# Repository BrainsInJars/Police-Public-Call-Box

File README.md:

Police-Public-Call-Box
======================

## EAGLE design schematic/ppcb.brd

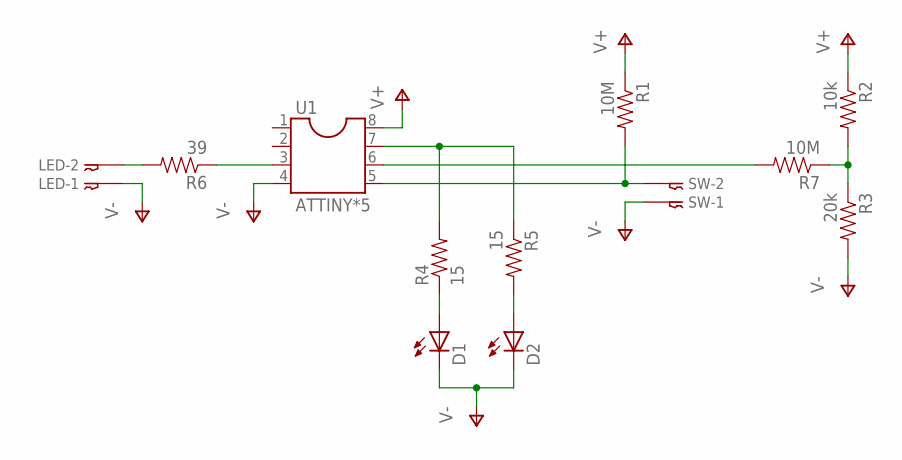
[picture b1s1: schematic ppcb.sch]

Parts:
D1, D2: LED5MM
LED: 02-JST; B2B-XH
R1, R7: 10M; AXIAL-0.4
R2: 10k; AXIAL-0.4
R3: 20k; AXIAL-0.4
R4, R5: 15; AXIAL-0.4
R6: 39; AXIAL-0.4
SW: 02-JST; B2B-XH
U1: ATTINY*5; SOCKET-08

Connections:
unnamed: R1.P$2 (2), SW.P$2, U1.5
unnamed: R7.P$2 (2), U1.6
unnamed: LED.P$2, R6.P$2 (2)
unnamed: D1.A, R4.P$1 (1)
unnamed: R2.P$2 (2), R3.P$1 (1), R7.P$1 (1)
unnamed: D2.A, R5.P$2 (2)
unnamed: R6.P$1 (1), U1.3
unnamed: R4.P$2 (2), R5.P$1 (1), U1.7
V+: R1.P$1 (1), R2.P$1 (1), U1.8
V-: D1.K (C), D2.K (C), LED.P$1, R3.P$2 (2), SW.P$1, U1.4

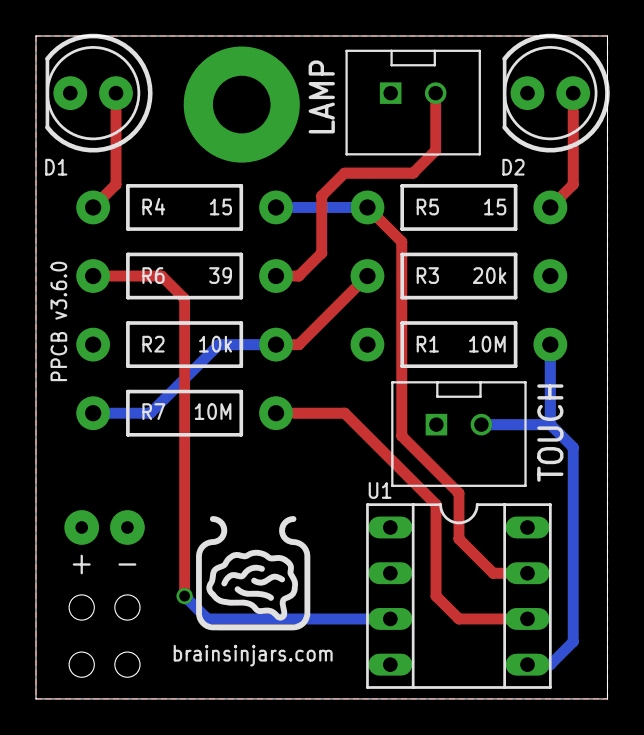
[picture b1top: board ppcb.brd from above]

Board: 4 copper layers, 31.8 x 36.8 mm, 13 parts (0 on the bottom side), 10 nets.

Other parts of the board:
U$2: LOGO-1_4_IN

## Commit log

2013-12-02 Added ignores for compiled *.elf and *.hex files
2013-12-02 Initial source code commit
2013-12-02 Added v3.5.0 schematic and board files
2013-12-02 Updated code to use internal analog comparator instead of an external LM211 and the external interrupt
2013-12-02 Updated PCB to remove external analog comparator and make use of Timer/Counter-1 instead of Timer/Counter-0
2014-07-23 Added PCB gerber files for board fabrication
2015-01-06 Fixed a fuse issue
    The louse byte was being incorrectly set and causing clock issues
2015-01-06 Updated gerbers
2015-01-07 Generated missing top and bottom copper layers and fixed the missing top silkscreen

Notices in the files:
parts and their libraries:
SparkFun-Resistors: Licensing: CC v3.0 Share-Alike You are welcome to use this library for commercial purposes.
